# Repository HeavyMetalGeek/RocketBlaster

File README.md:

# RocketBlaster - Air Powered Rocket Launcher

### Current Requirements:

- Supplied with 18V-24V, likely with two 9V batteries
- Main toggle switch for controlling power to the system (lights red LED when closed)
- Secondary toggle switch will act as a safety switch (lights yellow LED when closed)
- A momentary switch will be used for triggering the launch (lights green LED during launch sequence)
- When the launch sequence is triggered, the microcontroller triggers playback of an audio file from the DFPlayer Mini (DFR0299) module
- After a time that correlates to the end of the audio playback, triggers a MOSFET to switch the 18V-24V source for the solenoid valve

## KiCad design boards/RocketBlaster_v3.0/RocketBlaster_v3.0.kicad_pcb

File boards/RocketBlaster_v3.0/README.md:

# RocketBlaster - PCB Design

### Design Parameters:
* Small form factor to reduce cost
* MCU programmed via ISP header
* Use JST connectors to connect to switches on enclosure
* Intended to mount to enclosure top, so that LEDs pertrude
* DFPlayer plugs into headers on bottom of PCB
* SD card in DFPlayer stores audio files

### Current State:
* PCB designed in KiCAD
* Prototype boards fabricated
* Components sourced and acquired
* 1 prototype assembled and ready for firmware testing

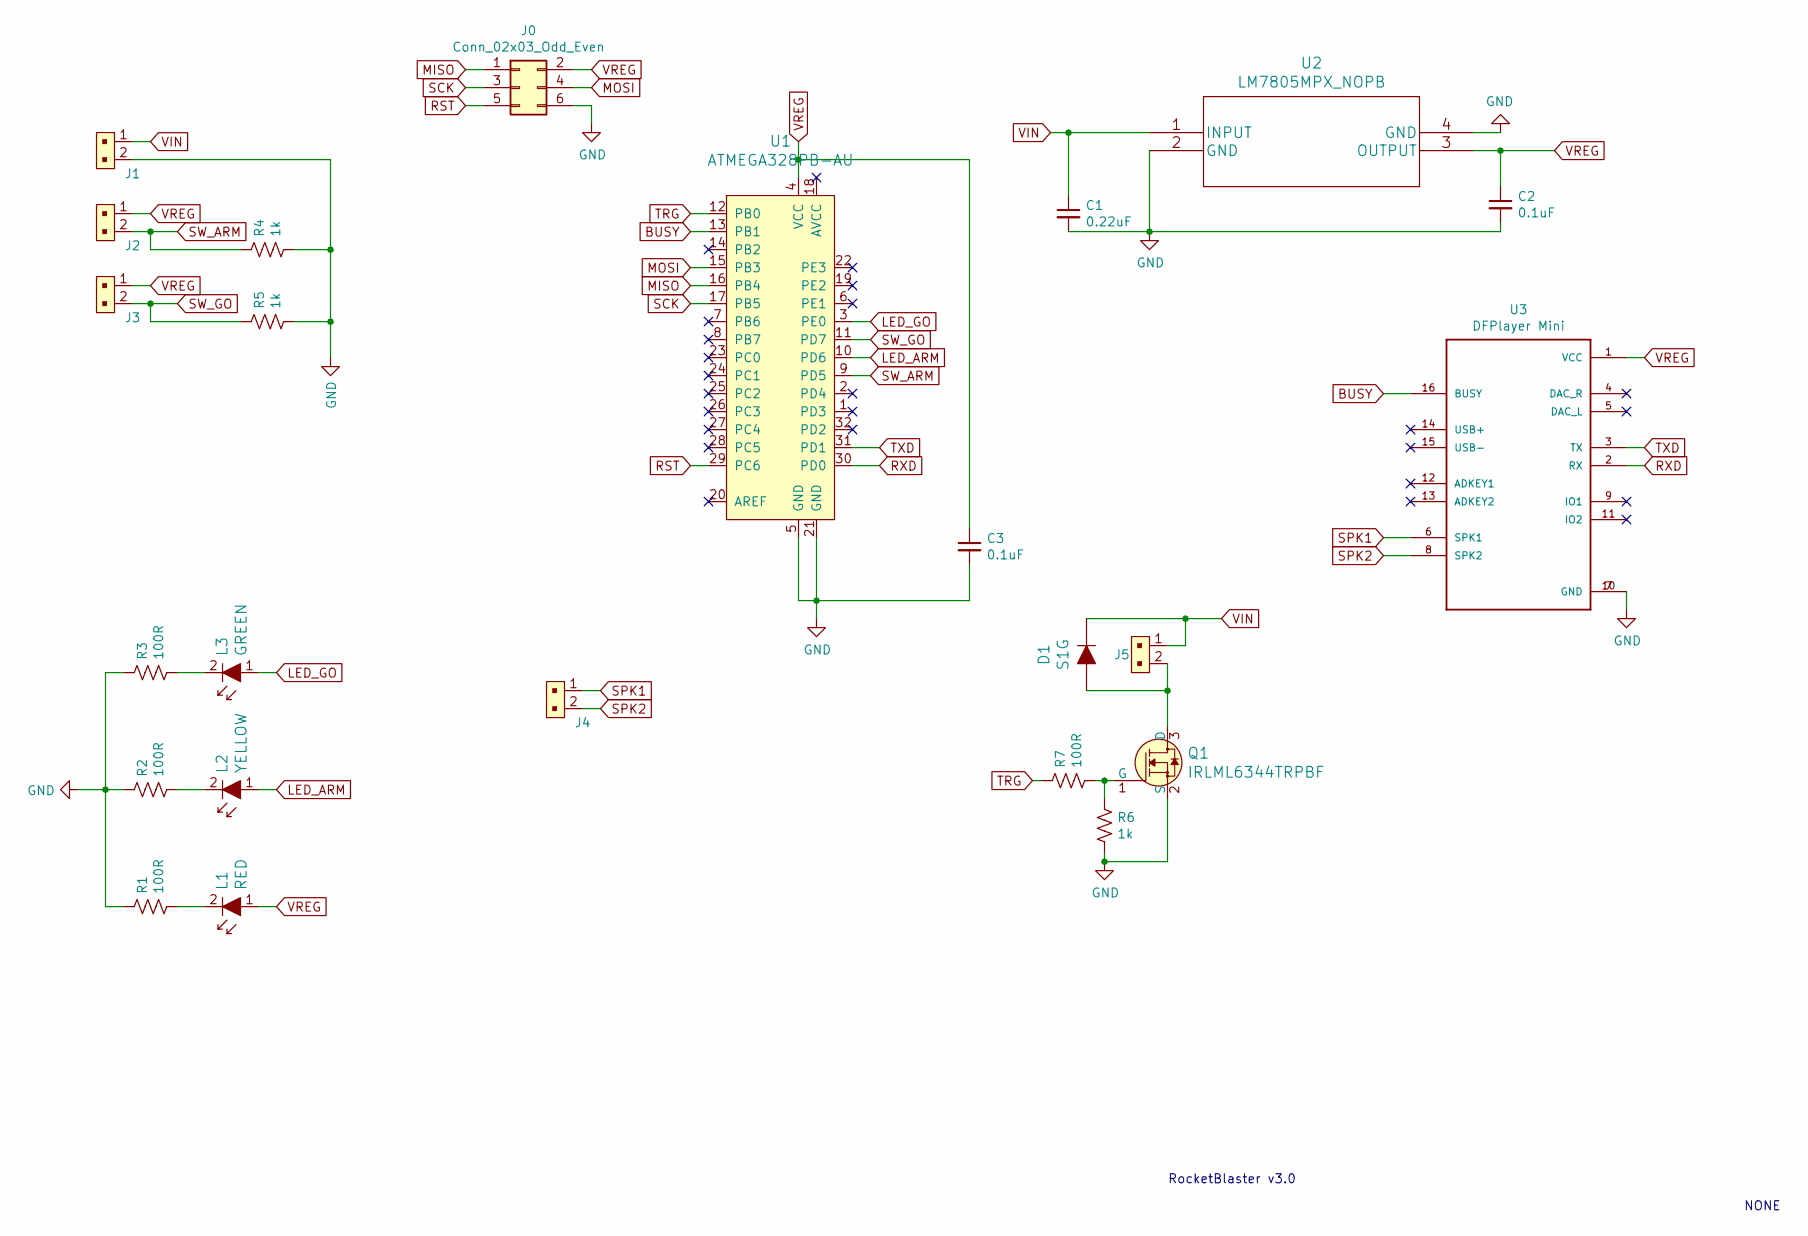
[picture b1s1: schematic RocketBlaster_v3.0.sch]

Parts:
C1: 0.22uF; C_0805_2012Metric
C2, C3: 0.1uF; C_0805_2012Metric
D1: S1G; DO-214AC; MPN S1G; Digi-Key_PN S1GFSCT-ND
J0: Conn_02x03_Odd_Even; PinHeader_2x03_P2.54mm_Vertical
J1, J2, J3, J4, J5: B2B-XH-A_LF__SN_; PinHeader_1x2_P2.5mm_Drill1.1mm; MPN B2B-XH-A(LF)(SN); Digi-Key_PN 455-2247-ND
L1: RED; LED_3mm_Radial; MPN 151033RS03000; Digi-Key_PN 732-5013-ND
L2: YELLOW; LED_3mm_Radial; MPN 151033RS03000; Digi-Key_PN 732-5013-ND
L3: GREEN; LED_3mm_Radial; MPN 151033RS03000; Digi-Key_PN 732-5013-ND
Q1: IRLML6344TRPBF; SOT-23-3; MPN IRLML6344TRPBF; Digi-Key_PN IRLML6344TRPBFCT-ND
R1, R2, R3, R7: 100R; R_0805_2012Metric
R4, R5, R6: 1k; R_0805_2012Metric
U1: ATMEGA328PB-AU; TQFP-32_7x7mm; MPN ATMEGA328PB-AU; Digi-Key_PN ATMEGA328PB-AU-ND
U2: LM7805MPX_NOPB; LM7805MPX&slash_NOPB
U3: DFPlayer Mini; MODULE_DFR0299

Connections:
BUSY: U1.13 (PB1), U3.16 (BUSY)
GND: C1.2, C2.2, C3.2, J0.6, J1.2, Q1.2 (S), R1.1, R2.1, R3.1, R4.2, R5.2, R6.2, U1.5 (GND), U1.21 (GND), U2.2 (GND), U2.4 (GND), U3.7 (GND), U3.10 (GND)
LED_ARM: L2.1, U1.10 (PD6)
LED_GO: L3.1, U1.3 (PE0)
MISO: J0.1, U1.16 (PB4)
MOSI: J0.4, U1.15 (PB3)
unnamed: D1.A, J5.2, Q1.3 (D)
unnamed: L1.2, R1.2
unnamed: L2.2, R2.2
unnamed: L3.2, R3.2
unnamed: Q1.1 (G), R6.1, R7.2
RST: J0.5, U1.29 (PC6)
RXD: U1.30 (PD0), U3.2 (RX)
SCK: J0.3, U1.17 (PB5)
SPK1: J4.1, U3.6 (SPK1)
SPK2: J4.2, U3.8 (SPK2)
SW_ARM: J2.2, R4.1, U1.9 (PD5)
SW_GO: J3.2, R5.1, U1.11 (PD7)
TRG: R7.1, U1.12 (PB0)
TXD: U1.31 (PD1), U3.3 (TX)
VIN: C1.1, D1.K, J1.1, J5.1, U2.1 (INPUT)
VREG: C2.1, C3.1, J0.2, J2.1, J3.1, L1.1, U1.4 (VCC), U2.3 (OUTPUT), U3.1 (VCC)

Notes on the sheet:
NONE
RocketBlaster v3.0

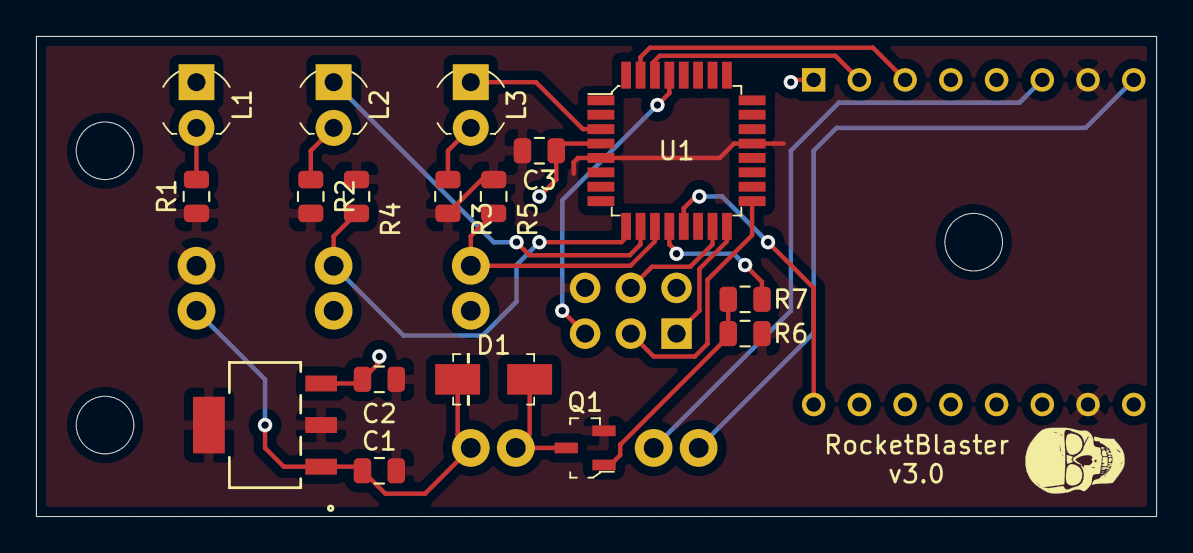
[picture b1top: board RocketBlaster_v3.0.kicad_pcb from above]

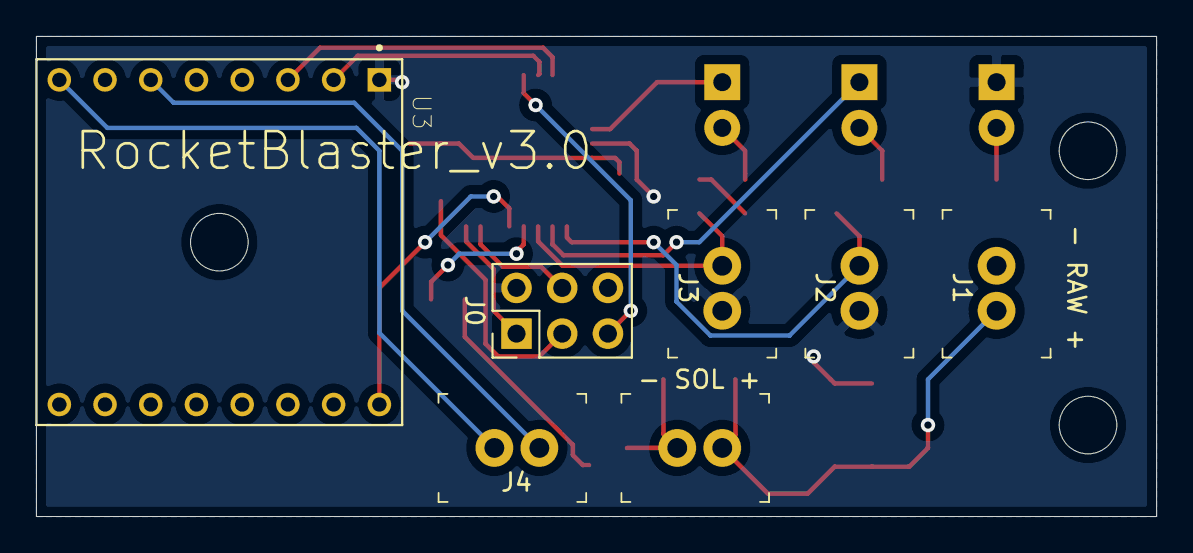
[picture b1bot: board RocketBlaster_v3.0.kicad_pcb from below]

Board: 2 copper layers, 62.2 x 26.7 mm, 24 parts (7 on the bottom side), 22 nets.

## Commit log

2020-01-21 Added image for current state of the schematic
2020-01-21 Added firmware and updated readme
2020-01-21 Modified readme text
2020-01-23 Corrections to schematic and PCB parameters for OSH Park
2021-04-17 Update KiCAD files, add enclosure folder, and add README info
2021-04-17 Corrected image path

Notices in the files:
parts and their libraries:
Copyright 2016 Accelerated Designs. All rights reserved.
